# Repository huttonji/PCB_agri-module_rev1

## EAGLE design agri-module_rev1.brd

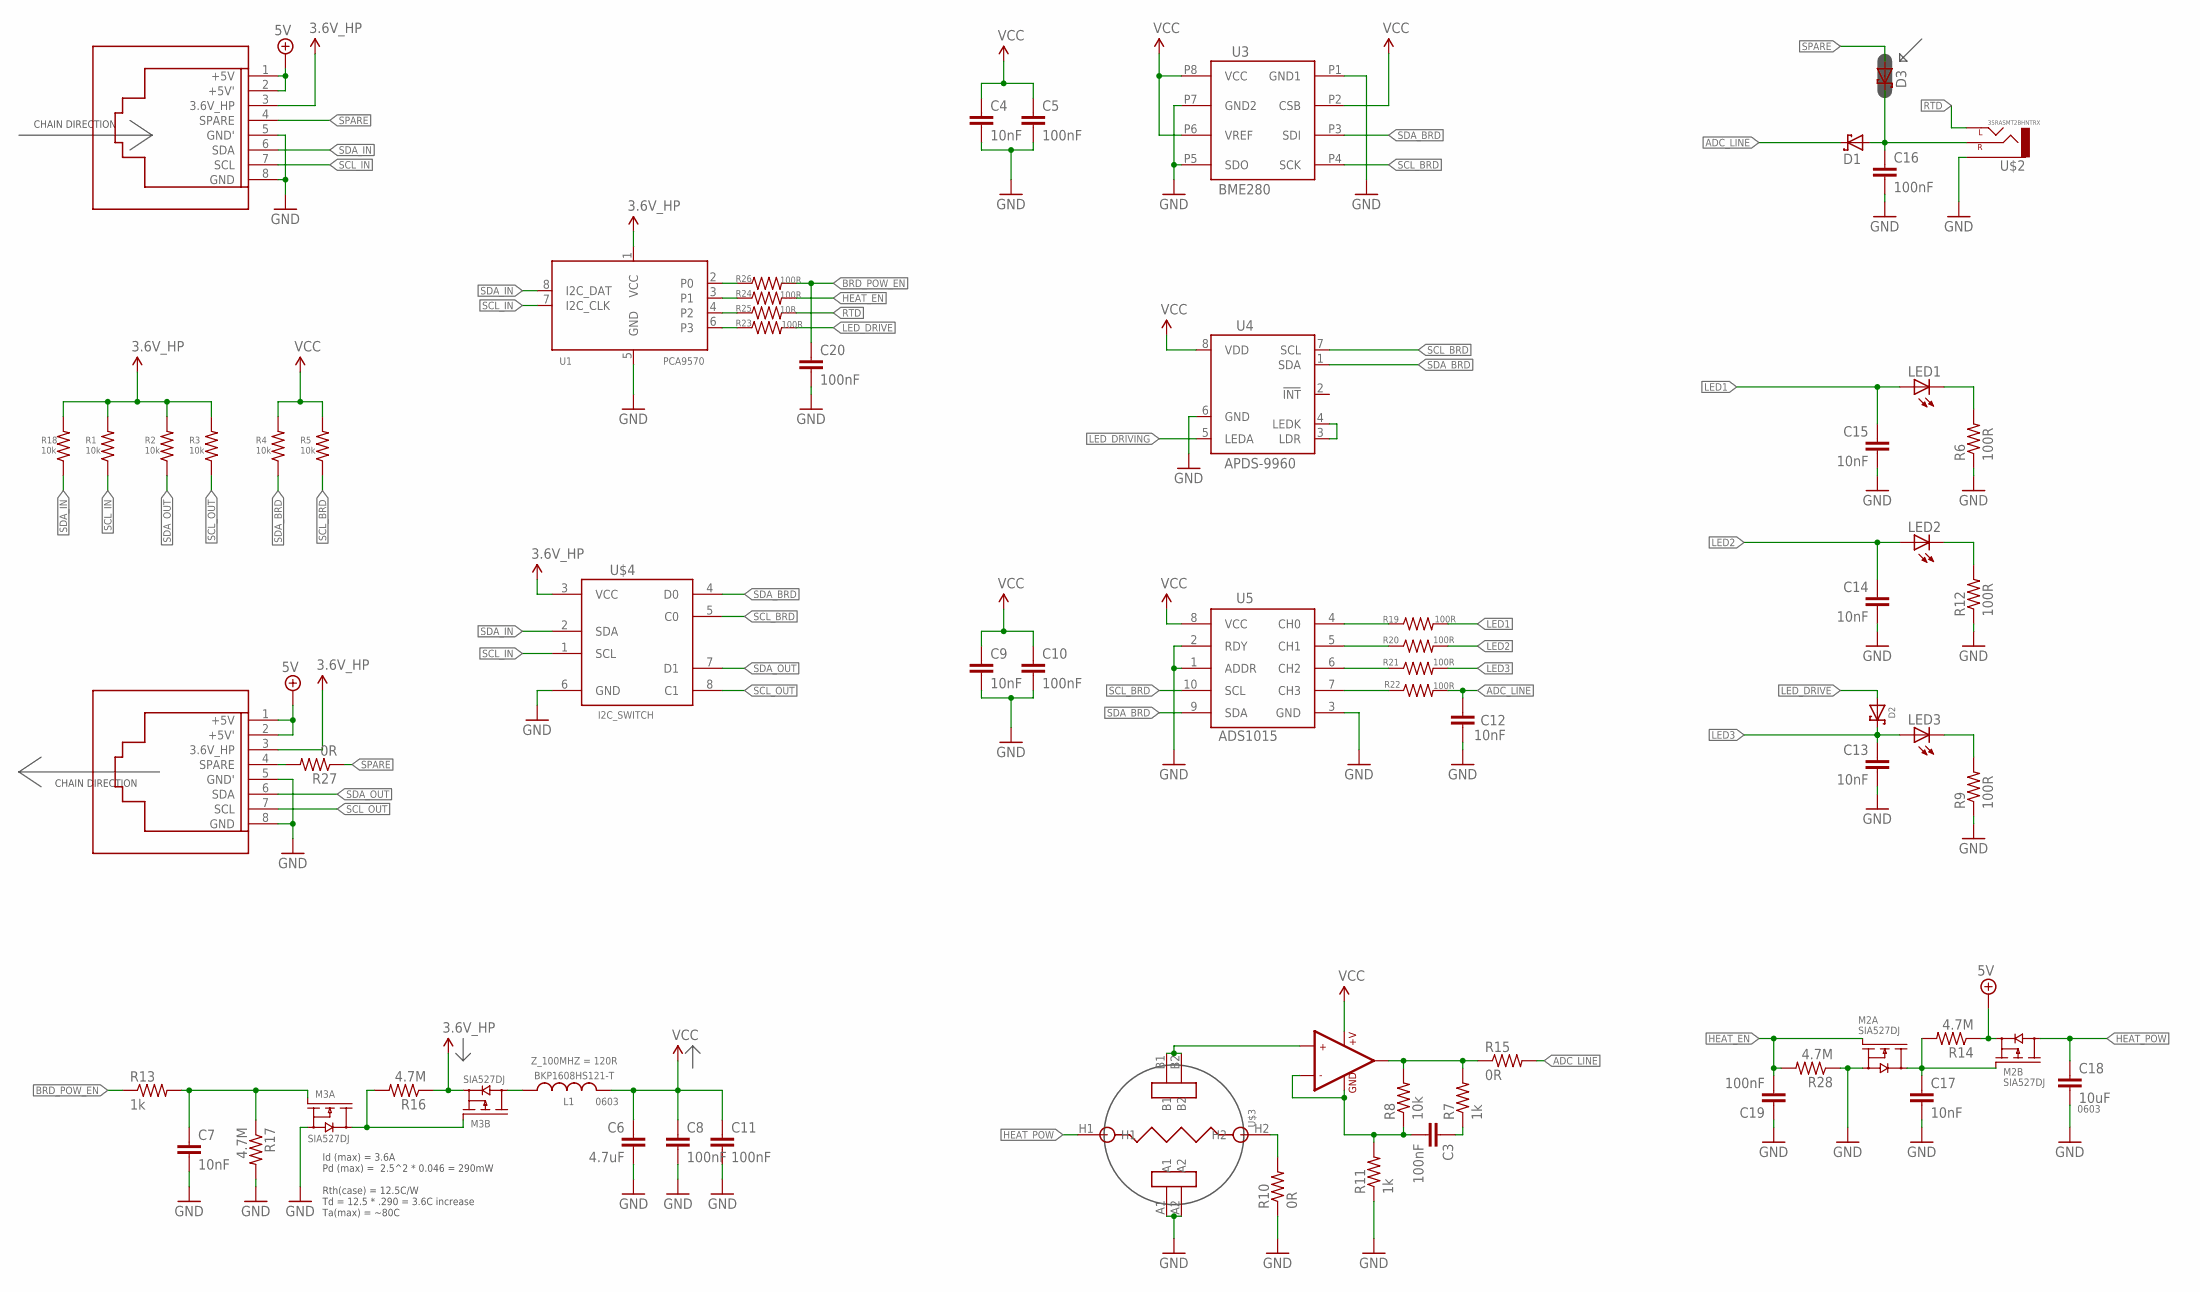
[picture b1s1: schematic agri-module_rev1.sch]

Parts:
C3, C5, C8, C10, C11, C16, C19, C20: 100nF; C0402-BG
C4, C7, C9, C12, C13, C14, C15, C17: 10nF; C0402-BG
C6: 4.7uF; C0402-BG
C18: 10uF; C0603-BG
D1, D2, D3: BAT54XV2; SOD523
L1: L-0603; 0603; MPN BKP1608HS121-T
LED1, LED2, LED3: LEDCHIPLED-0603-TTW; CHIPLED-0603-TTW
M2, M3: SIA527DJ; SC-70-6-L
R1, R2, R3, R4, R5, R8, R18: 10k; R0402-BG
R6, R9, R12, R19, R20, R21, R22, R23, R24, R26: 100R; R0402-BG
R7, R11, R13: 1k; R0402-BG
R10, R15, R27: 0R; R0402-BG
R14, R16, R17, R28: 4.7M; R0402-BG
R25: 10R; R0402-BG
U1: PCA9570; XQFN8
U3: BME280
U4: APDS-9960
U5: ADS1015
U$1, U$9: RJ45_RA_SMD
U$2: 35RASMT2BHNTRX; 35RASMTBHNTRX
U$3: MG811
U$4: I2C_SWITCH; SOT505-1
U$5: MCP6001T; SOT23-5

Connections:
3.6V_HP: M3.4 (S2), R1.2, R2.2, R3.2, R16.1, R18.2, U1.1 (VCC), U$1.3 (3.6V_HP), U$9.3 (3.6V_HP)
3.6V_HP_FILT: U$4.3 (VCC)
5V: M2.4 (S2), R14.1, U$1.1 (+5V), U$1.2 (+5V'), U$9.1 (+5V), U$9.2 (+5V')
ADC_LINE: C12.1, D1.C, R15.2, R22.2
BRD_POW_EN: C20.1, R13.1, R26.2
GND: C4.2, C5.2, C6.2, C7.2, C8.2, C9.2, C10.2, C11.2, C12.2, C13.2, C14.2, C15.2, C16.2, C17.2, C18.2, C19.1, C20.2, M2.1 (S1), M3.1 (S1), R6.1, R9.1, R10.1, R11.1, R12.1, R17.2, R28.1, U1.5 (GND), U3.P1 (GND1), U3.P5 (SDO), U3.P7 (GND2), U4.6 (GND), U5.1 (ADDR), U5.2 (RDY), U5.3 (GND), U$1.5 (GND'), U$1.8 (GND), U$2.5 (SLEEVE), U$3.A1, U$3.A2, U$4.6 (GND), U$9.5 (GND'), U$9.8 (GND)
HEAT_EN: C19.2, M2.2 (G1), R24.2, R28.2
HEAT_POW: C18.1, M2.3 (D2), M2.TAB2 (D2), U$3.H1
HOST_POW_EN: C7.1, M3.2 (G1), R13.2, R17.1
LED1: C15.1, LED1.A@1 (A), R19.2
LED2: C14.1, LED2.A@1 (A), R20.2
LED3: C13.1, D2.C, LED3.A@1 (A), R21.2
LED_DRIVE: D2.A, R23.2
LED_DRIVING: U4.5 (LEDA)
M$65: R21.1, U5.6 (CH2)
unnamed: R26.1, U1.2 (P0)
unnamed: U4.3 (LDR), U4.4 (LEDK)
unnamed: C16.1, D1.A, D3.C, U$2.1 (RIGHT)
unnamed: LED1.C@1 (C), R6.2
unnamed: C3.2, R8.1, R11.2, U$5.2 (GND), U$5.4 (-IN1)
unnamed: R24.1, U1.3 (P1)
unnamed: U$3.B1, U$3.B2, U$5.3 (+IN1)
unnamed: R7.2, R8.2, R15.1, U$5.1 (OUT1)
unnamed: LED2.C@1 (C), R12.2
unnamed: LED3.C@1 (C), R9.2
unnamed: L1.1, M3.3 (D2), M3.TAB2 (D2)
unnamed: R25.1, U1.4 (P2)
unnamed: C17.1, M2.5 (G2), M2.6 (D1), M2.TAB1 (D1), R14.2
unnamed: R23.1, U1.6 (P3)
unnamed: R27.2, U$9.4 (SPARE)
unnamed: R10.2, U$3.H2
unnamed: C3.1, R7.1
unnamed: M3.5 (G2), M3.6 (D1), M3.TAB1 (D1), R16.2
unnamed: R19.1, U5.4 (CH0)
unnamed: R20.1, U5.5 (CH1)
unnamed: R22.1, U5.7 (CH3)
RTD: R25.2, U$2.4 (LEFT)
SCL_BRD: R5.1, U3.P4 (SCK), U4.7 (SCL), U5.10 (SCL), U$4.5 (C0)
SCL_IN: R1.1, U1.7 (I2C_CLK), U$1.7 (SCL), U$4.1 (SCL)
SCL_OUT: R3.1, U$4.8 (C1), U$9.7 (SCL)
SDA_BRD: R4.1, U3.P3 (SDI), U4.1 (SDA), U5.9 (SDA), U$4.4 (D0)
SDA_IN: R18.1, U1.8 (I2C_DAT), U$1.6 (SDA), U$4.2 (SDA)
SDA_OUT: R2.1, U$4.7 (D1), U$9.6 (SDA)
SPARE: D3.A, R27.1, U$1.4 (SPARE)
VCC: C4.1, C5.1, C6.1, C8.1, C9.1, C10.1, C11.1, L1.2, R4.2, R5.2, U3.P2 (CSB), U3.P6 (VREF), U3.P8 (VCC), U4.8 (VDD), U5.8 (VCC), U$5.5 (+V)

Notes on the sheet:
CHAIN DIRECTION
Id (max) = 3.6A Pd (max) = 2.5^2 * 0.046 = 290mW Rth(case) = 12.5C/W Td = 12.5 * .290 = 3.6C increase Ta(max) = ~80C

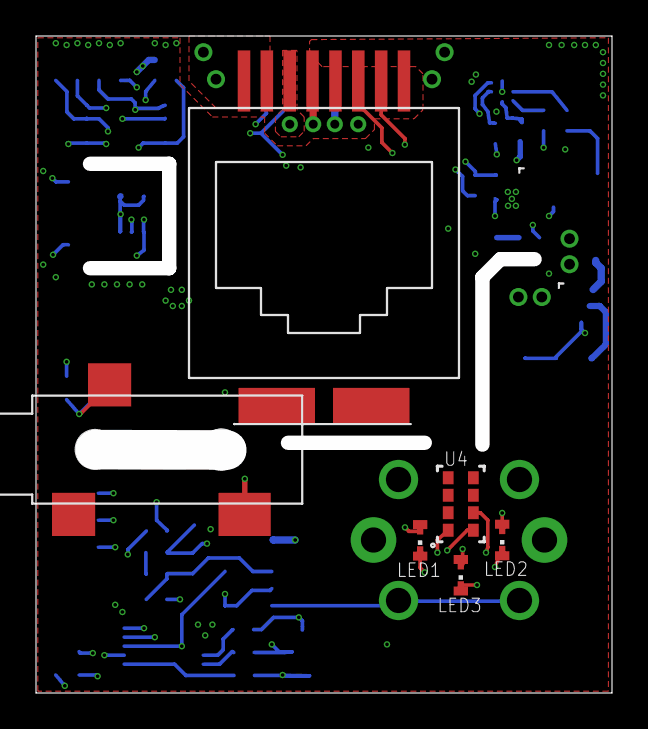
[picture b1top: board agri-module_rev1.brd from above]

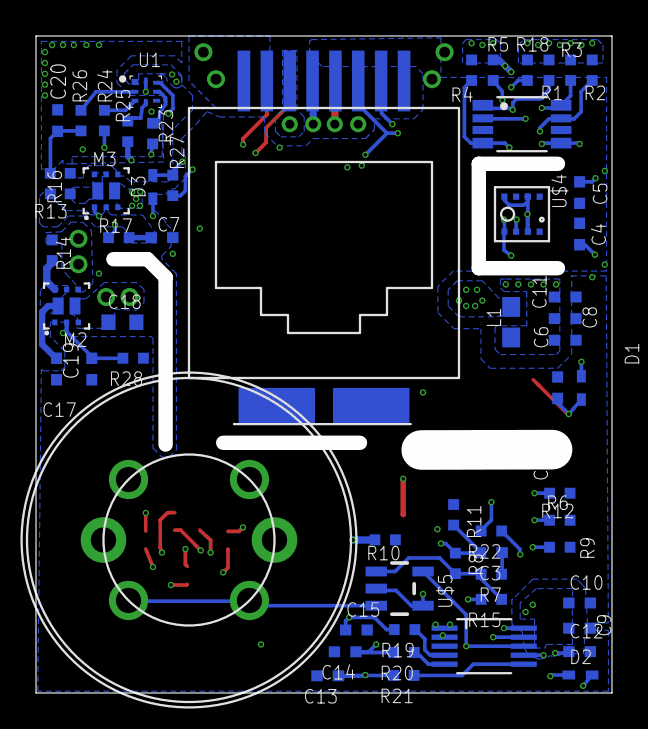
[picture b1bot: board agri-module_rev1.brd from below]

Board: 4 copper layers, 32.0 x 36.5 mm, 65 parts (59 on the bottom side), 43 nets.

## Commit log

2016-08-12 :octocat: Added .gitattributes
2016-08-12 First save of blank brd and sch files
2016-08-12 Added most components
    -still need ISL and Co2
2016-08-12 ignore s## and b##
2016-08-12 add ISL and new RJ45 pinout
2016-08-15 Everything wired up, not looked over yet
    -replaced ISL with RGB gesture
    -added hot film amp and CO2 amp
2016-08-15 Added indication use for one of LEDs
    -also connected EC_pow correctly
2016-08-15 Added name
2016-08-16 Initial Board Layout
2016-08-18 Audit 1 w/ notes (wired / ready for feedback...)
    ______________________________________________
    Schematic Feedback:
    ______________________________________________|
    -no "zero length" junctions to parts
    -add more labels, less long/jumbled connections
    -tighten up the look
2016-08-18 RIPUP;
    Just ripped up all lines to prepare for round 2 of layout
2016-08-22 fixed continuity errors

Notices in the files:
parts and their libraries:
SparkFun-AnalogIC: Licensing: CC v3.0 Share-Alike You are welcome to use this library for commercial purposes.
